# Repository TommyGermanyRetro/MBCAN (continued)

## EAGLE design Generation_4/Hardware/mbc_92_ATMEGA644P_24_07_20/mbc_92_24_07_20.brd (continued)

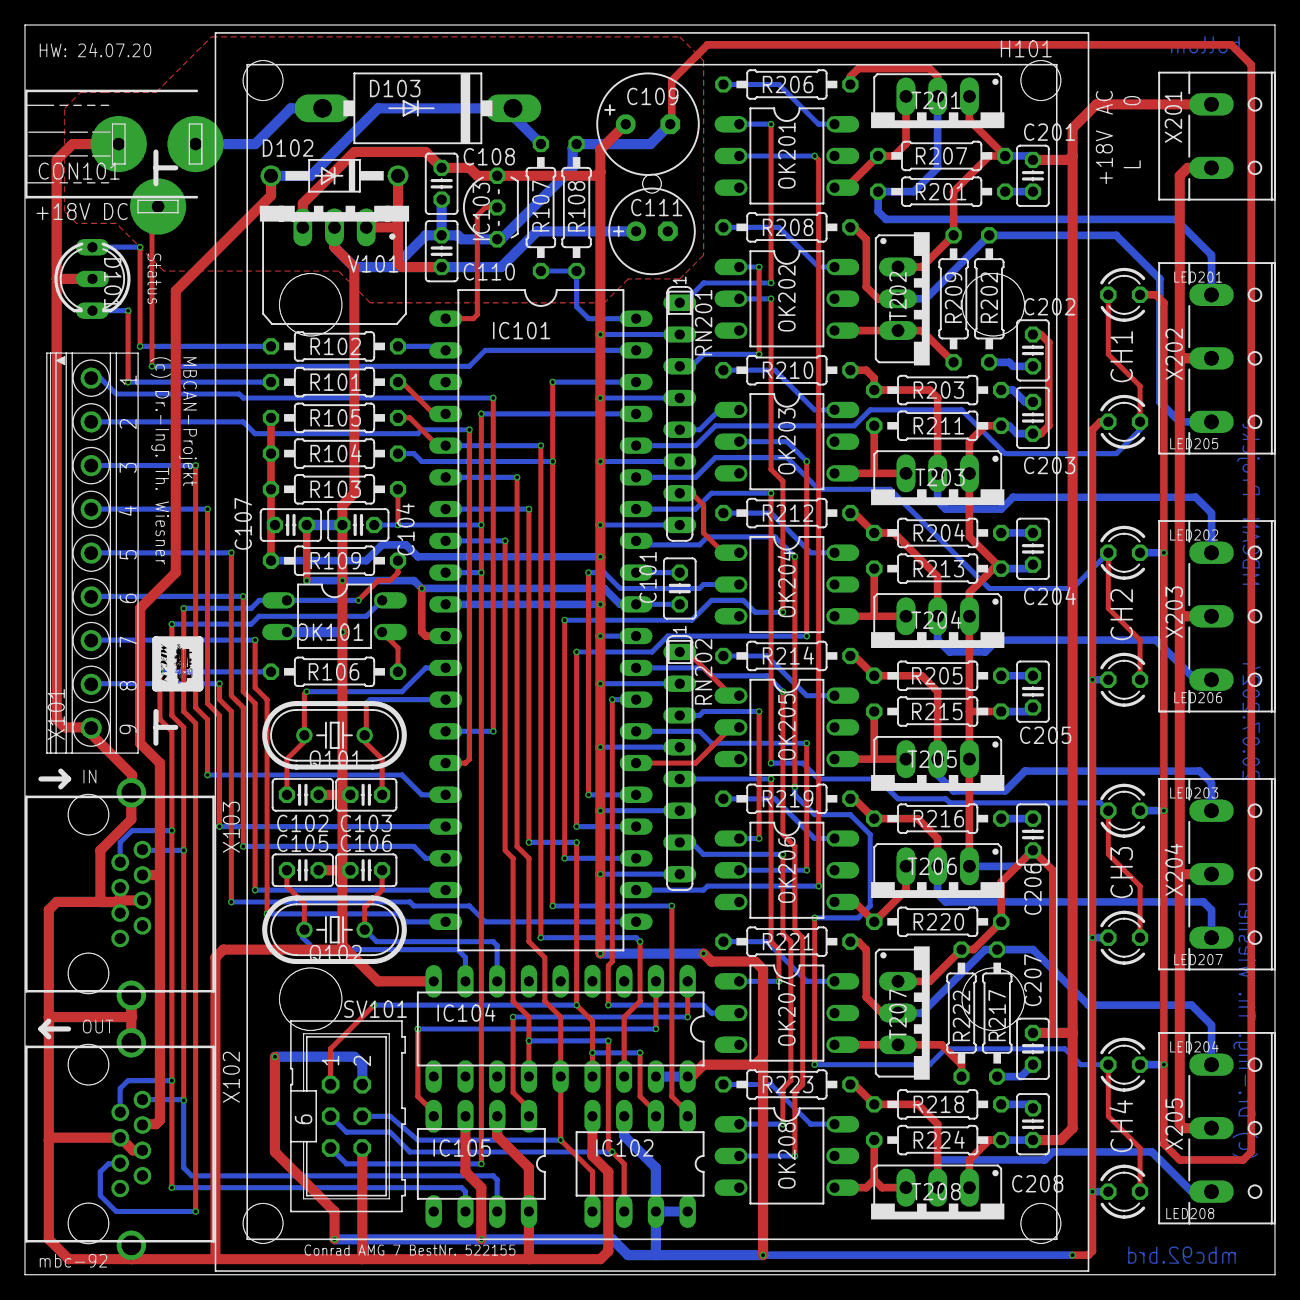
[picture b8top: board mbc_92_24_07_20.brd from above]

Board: 2 copper layers, 100.0 x 100.0 mm, 101 parts (0 on the bottom side), 91 nets.
